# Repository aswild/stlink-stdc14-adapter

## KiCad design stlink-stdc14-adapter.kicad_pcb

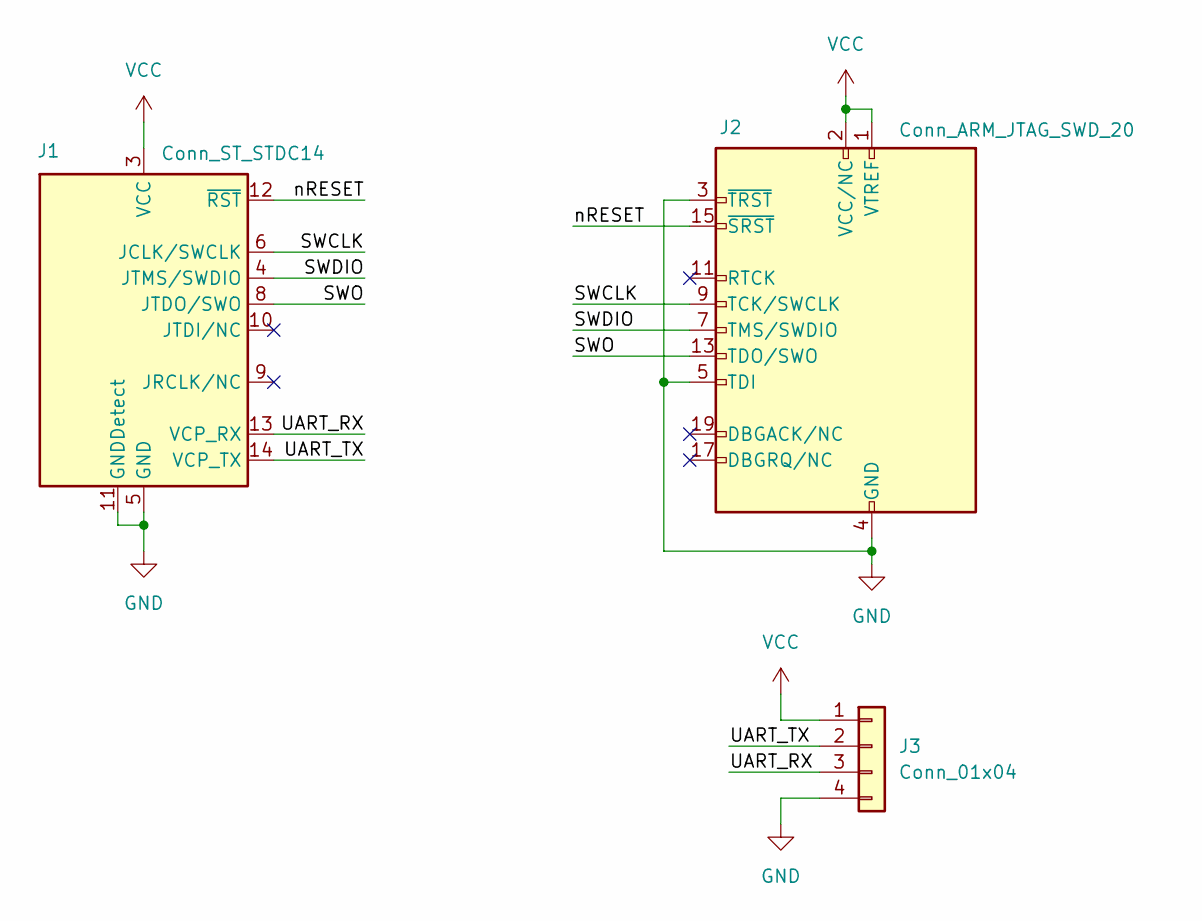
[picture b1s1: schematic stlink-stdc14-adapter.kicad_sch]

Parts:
J1: Conn_ST_STDC14; Samtec_FTSH_PinHeader_2x07_P1.27mm_Vertical_Keyed
J2: Conn_ARM_JTAG_SWD_20; IDC-Header_2x10_P2.54mm_Vertical
J3: Conn_01x04; PinHeader_1x04_P2.54mm_Vertical

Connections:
/SWCLK: J1.6 (JCLK/SWCLK), J2.9 (TCK/SWCLK)
/SWDIO: J1.4 (JTMS/SWDIO), J2.7 (TMS/SWDIO)
/SWO: J1.8 (JTDO/SWO), J2.13 (TDO/SWO)
/UART_RX: J1.13 (VCP_RX), J3.3
/UART_TX: J1.14 (VCP_TX), J3.2
/nRESET: J1.12 (~RST), J2.15 (~SRST)
GND: J1.5 (GND), J1.7 (GND), J1.11 (GNDDetect), J2.3 (~TRST), J2.4 (GND), J2.5 (TDI), J2.6 (GND), J2.8 (GND), J2.10 (GND), J2.12 (GND), J2.14 (GND), J2.16 (GND), J2.18 (GND), J2.20 (GND), J3.4
VCC: J1.3 (VCC), J2.1 (VTREF), J2.2 (VCC/NC), J3.1

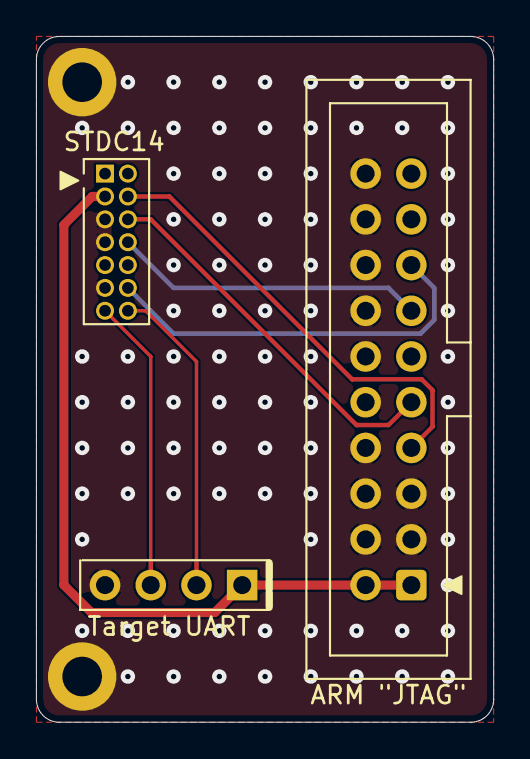
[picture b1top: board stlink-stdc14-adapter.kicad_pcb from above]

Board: 2 copper layers, 25.4 x 38.1 mm, 3 parts (0 on the bottom side), 8 nets.

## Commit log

2026-05-22 initial commit, draft of the adapter board
2026-05-27 rename project to stlink-stdc14-adapter
2026-05-27 swap RX and TX on the UART header
    Yep, I was wrong on the 50/50 guess, as is tradition.
2026-05-28 kinda redo the whole layout for a smaller board
    1.5" x 1" size, no more mounting holes. Smaller = cheaper.
2026-05-29 re-route, add silkscreen and via stitching
2026-05-29 rotate UART header
    To make more room on the side of the STDC14 so there's enough space to
    grab the plug comfortably.
2026-05-29 add mounting holes, move UART slightly farther from JTAG
2026-05-29 put "JTAG" in quotes on the silkscreen
